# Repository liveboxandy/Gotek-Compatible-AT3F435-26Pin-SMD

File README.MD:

Initial schematic and gerbers for a Gotek(?) compatible with an Artery AT32F435RGT7 chip and a 26 Pin FFC connector using SMD components.
Used SFRKC30.AT4.35 PCB for most of the schematic and layout but used SFRC2D.B PCB for the 26 Pin FFC connections.
Used photographs and a multimeter along with removing U1 and U3 on the SFRKC30.AT4.35 to get to the traces underneath.
Where possible I followed the original PCB routing of the SFRKC30.AT4.35 but Kicad has some different rules for trace widths (between pins 5&6 of U8).
Using SMD components required a few more routing changes but electrically it should still be good.

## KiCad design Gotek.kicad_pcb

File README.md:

# Gotek-Compatible-AT3F435-26Pin-SMD

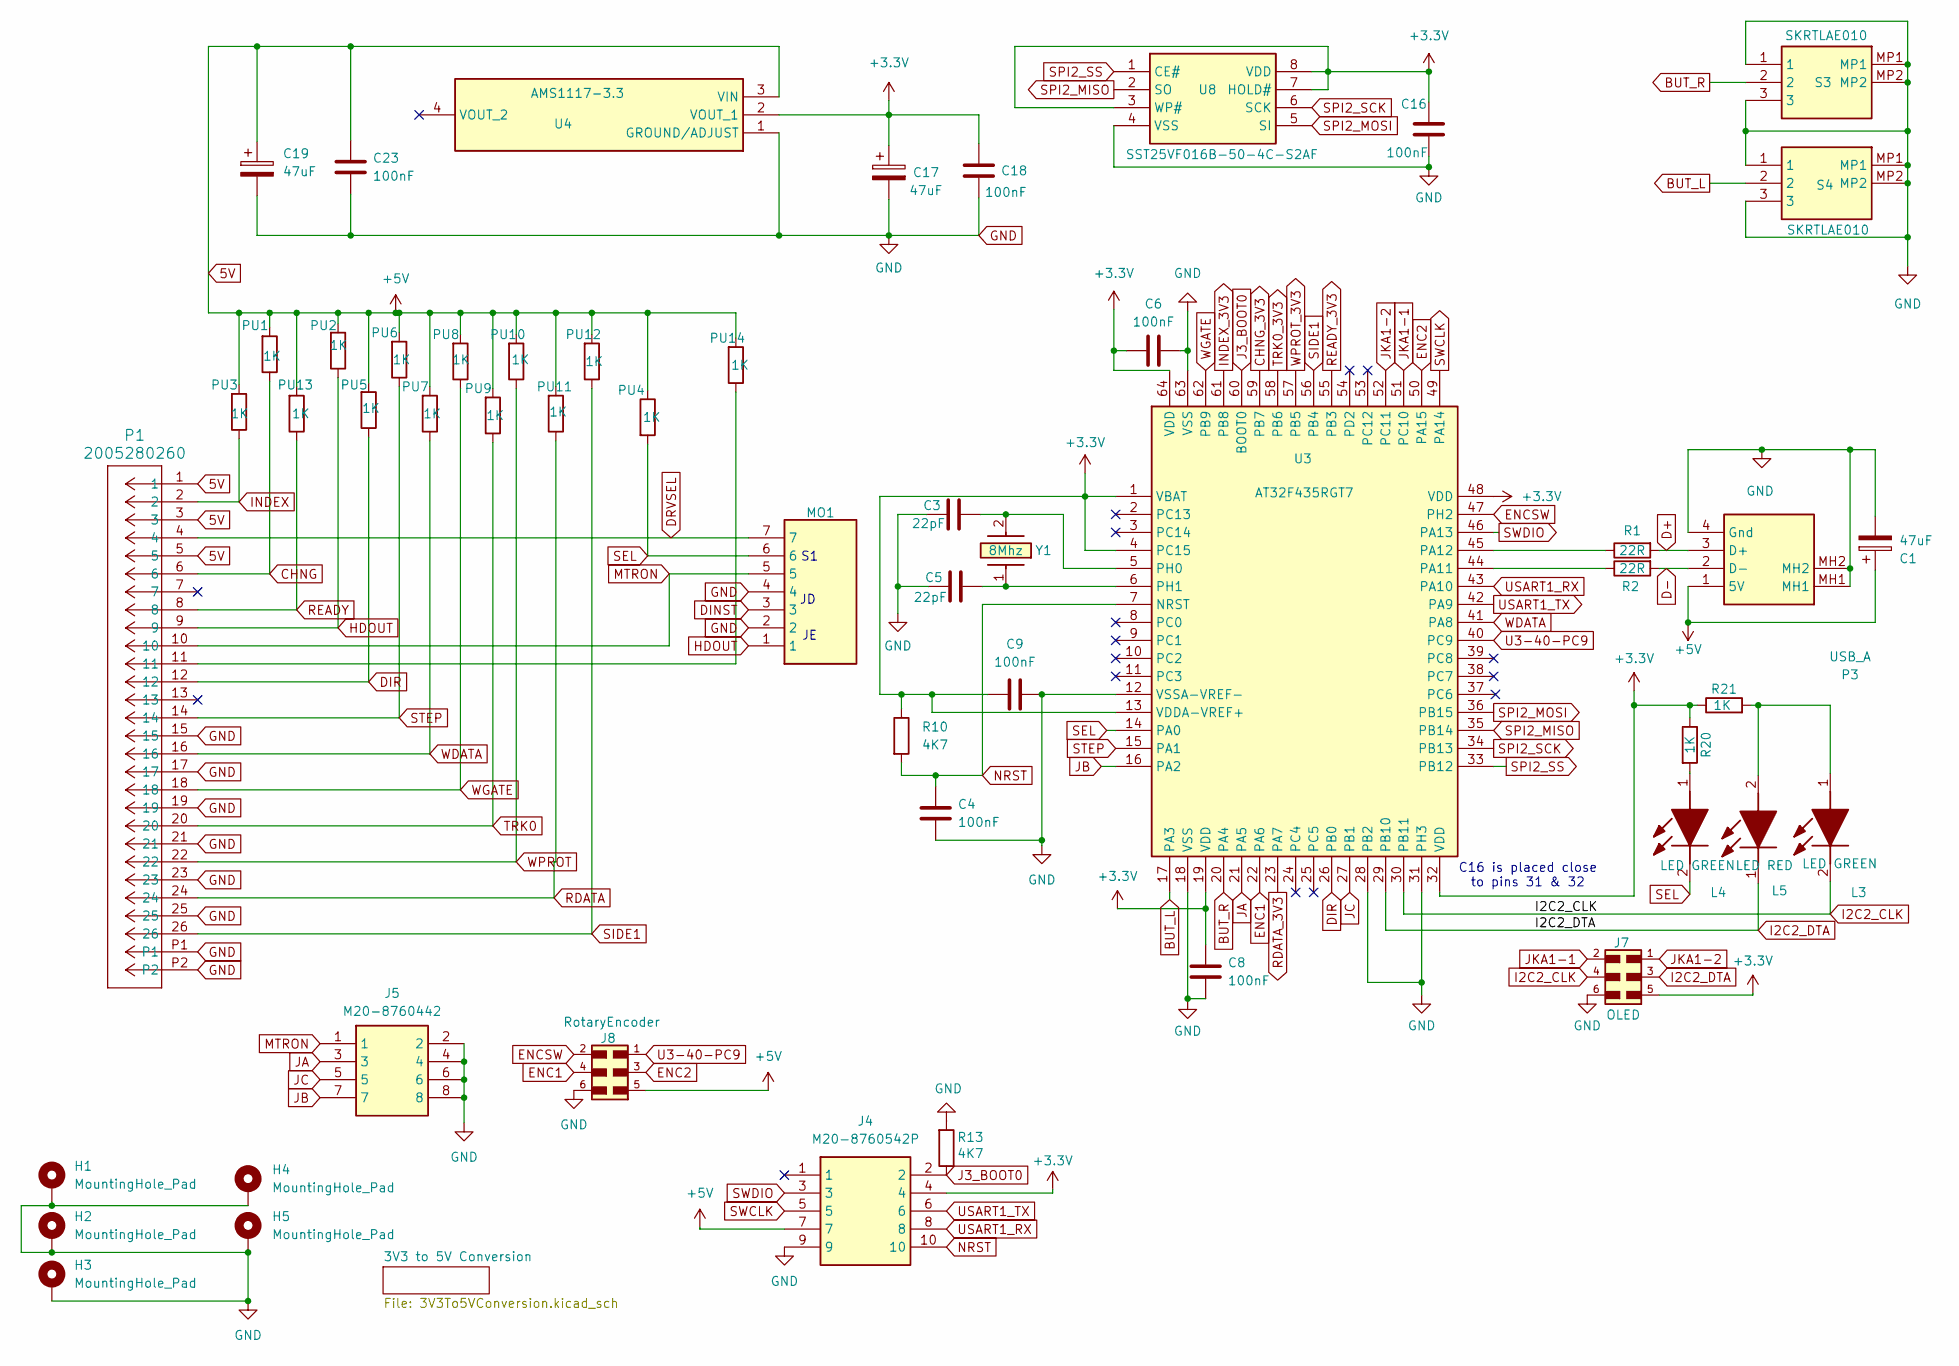
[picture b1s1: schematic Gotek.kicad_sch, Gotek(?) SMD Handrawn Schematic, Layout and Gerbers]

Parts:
C1, C17, C19: 47uF; CP_EIA-3528-21_Kemet-B_Pad1.50x2.35mm_HandSolder
C3, C5: 22pF; C_0805_2012Metric_Pad1.18x1.45mm_HandSolder
C4, C6, C8, C9, C16, C18, C23: 100nF; C_0805_2012Metric_Pad1.18x1.45mm_HandSolder
H1, H2, H3, H4, H5: MountingHole_Pad; MountingHole_M3_Pad
J4: M20-8760542P; HUSSP10W64P254_2X5_1270X500X1043P; Mouser Part Number 855-M20-8760542P
J5: M20-8760442; M208760442; Mouser Part Number 855-M20-8760442
J7: OLED; 610106249121
J8: RotaryEncoder; 610106249121
L3, L4: LED GREEN; APT2012PGW; Mouser Part Number 604-APT2012PGW
L5: LED RED; HSMCC177; Mouser Part Number 630-HSMC-C177
MO1: Conn_01x03_Pin; M208900705; Mouser Part Number 855-M20-8900705
P1: 2005280260; MOLEX_CON_2005280260
P3: USB_A; USB1046GF0190LBA; Mouser Part Number 640-USB1046GF0190LBA
PU1, PU2, PU3, PU4, PU5, PU6, PU7, PU8, PU9, PU10, PU11, PU12, PU13, PU14: 1K; R_0805_2012Metric_Pad1.20x1.40mm_HandSolder
R1, R2: 22R; R_0805_2012Metric_Pad1.20x1.40mm_HandSolder
R10, R13: 4K7; R_0805_2012Metric_Pad1.20x1.40mm_HandSolder
R20, R21: 1K; R_0805_2012Metric_Pad1.20x1.40mm_HandSolder
S3, S4: SKRTLAE010; Mouser Part Number 688-SKRTLA
U3: AT32F435RGT7; QFP50P1200X1200X160-64N; Manufacturer_Part_Number AT32F435RGT7
U4: AMS1117-3.3; SOT229P700X180-4N; Manufacturer_Part_Number ams1117-3.3v
U8: SST25VF016B-50-4C-S2AF; SOIC127P790X216-8N; Mouser Part Number 579-25VF016B504CS2AF
Y1: 8Mhz; LFXTAL050985Bulk; Mouser Part Number 449-LFXTAL050985BULK

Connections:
5V: C1.1, C19.1, C23.1, J4.7, J8.5, P1.1, P1.3, P1.5, P3.1 (5V), PU1.2, PU2.2, PU3.2, PU4.1, PU5.2, PU6.2, PU7.2, PU8.2, PU9.2, PU10.2, PU11.2, PU12.2, PU13.2, PU14.2, U4.3 (VIN); also elsewhere on the board
+3.3V: C6.1, C8.1, C9.2, C16.2, C17.1, C18.2, J4.4, J7.5, R10.1, R20.1, R21.1, U3.1 (VBAT), U3.4 (PC15), U3.13 (VDDA-VREF+), U3.19 (VDD), U3.32 (VDD), U3.48 (VDD), U3.64 (VDD), U4.2 (VOUT_1), U8.3 (WP#), U8.7 (HOLD#), U8.8 (VDD)
BUT_L: S4.2, U3.17 (PA3)
BUT_R: S3.2, U3.20 (PA4)
CHNG: P1.6, PU1.1; also elsewhere on the board
CHNG_3V3: U3.59 (PB7); also elsewhere on the board
D+: P3.3 (D+), R1.2
D-: P3.2 (D-), R2.2
DINST: MO1.3
DIR: P1.12, PU5.1, U3.26 (PB0)
DRVSEL: MO1.7, P1.4
ENC1: J8.4, U3.22 (PA6)
ENC2: J8.3, U3.50 (PA15)
ENCSW: J8.2, U3.47 (PH2)
GND: C1.2, C3.1, C4.2, C5.2, C6.2, C8.2, C9.1, C16.1, C17.2, C18.1, C19.2, C23.2, H1.1, H2.1, H3.1, H4.1, H5.1, J4.9, J5.2, J5.4, J5.6, J5.8, J7.6, J8.6, MO1.2, MO1.4, P1.15, P1.17, P1.19, P1.21, P1.23, P1.25, P1.P1, P1.P2, P3.4 (Gnd), P3.MH1, P3.MH2, R13.2, S3.1, S3.3, S3.MP1, S3.MP2, S4.1, S4.3, S4.MP1, S4.MP2, U3.12 (VSSA-VREF-), U3.18 (VSS), U3.28 (PB2), U3.31 (PH3), U3.63 (VSS), U4.1 (GROUND/ADJUST), U8.4 (VSS); also elsewhere on the board
HDOUT: MO1.1, P1.9, PU2.1
I2C2_CLK: J7.4, L3.2 (K), U3.30 (PB11)
I2C2_DTA: J7.3, L5.1 (K), U3.29 (PB10)
INDEX: P1.2, PU3.1; also elsewhere on the board
INDEX_3V3: U3.61 (PB8); also elsewhere on the board
J3_BOOT0: J4.2, R13.1, U3.60 (BOOT0)
JA: J5.3, U3.21 (PA5)
JB: J5.7, U3.16 (PA2)
JC: J5.5, U3.27 (PB1)
JKA1-1: J7.2, U3.51 (PC10)
JKA1-2: J7.1, U3.52 (PC11)
MTRON: J5.1, MO1.5, P1.10
NRST: C4.1, J4.10, R10.2, U3.7 (NRST)
unnamed: L3.1 (A), L5.2 (A), R21.2
unnamed: L4.1 (A), R20.2
unnamed: P1.11, PU14.1
unnamed: R2.1, U3.44 (PA11)
unnamed: R1.1, U3.45 (PA12)
unnamed: C3.2, U3.5 (PH0), Y1.2
unnamed: C5.1, U3.6 (PH1), Y1.1
RDATA: P1.24, PU11.1; also elsewhere on the board
RDATA_3V3: U3.23 (PA7); also elsewhere on the board
READY: P1.8, PU13.1; also elsewhere on the board
READY_3V3: U3.55 (PB3); also elsewhere on the board
SEL: L4.2 (K), MO1.6, PU4.2, U3.14 (PA0)
SIDE1: P1.26, PU12.1, U3.56 (PB4)
SPI2_MISO: U3.35 (PB14), U8.2 (SO)
SPI2_MOSI: U3.36 (PB15), U8.5 (SI)
SPI2_SCK: U3.34 (PB13), U8.6 (SCK)
SPI2_SS: U3.33 (PB12), U8.1 (CE#)
STEP: P1.14, PU6.1, U3.15 (PA1)
SWCLK: J4.5, U3.49 (PA14)
SWDIO: J4.3, U3.46 (PA13)
TRK0: P1.20, PU9.1; also elsewhere on the board
TRK0_3V3: U3.58 (PB6); also elsewhere on the board
U3-40-PC9: J8.1, U3.40 (PC9)
USART1_RX: J4.8, U3.43 (PA10)
USART1_TX: J4.6, U3.42 (PA9)
WDATA: P1.16, PU7.1, U3.41 (PA8)
WGATE: P1.18, PU8.1, U3.62 (PB9)
WPROT: P1.22, PU10.1; also elsewhere on the board
WPROT_3V3: U3.57 (PB5); also elsewhere on the board

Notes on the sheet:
C16 is placed close to pins 31 & 32

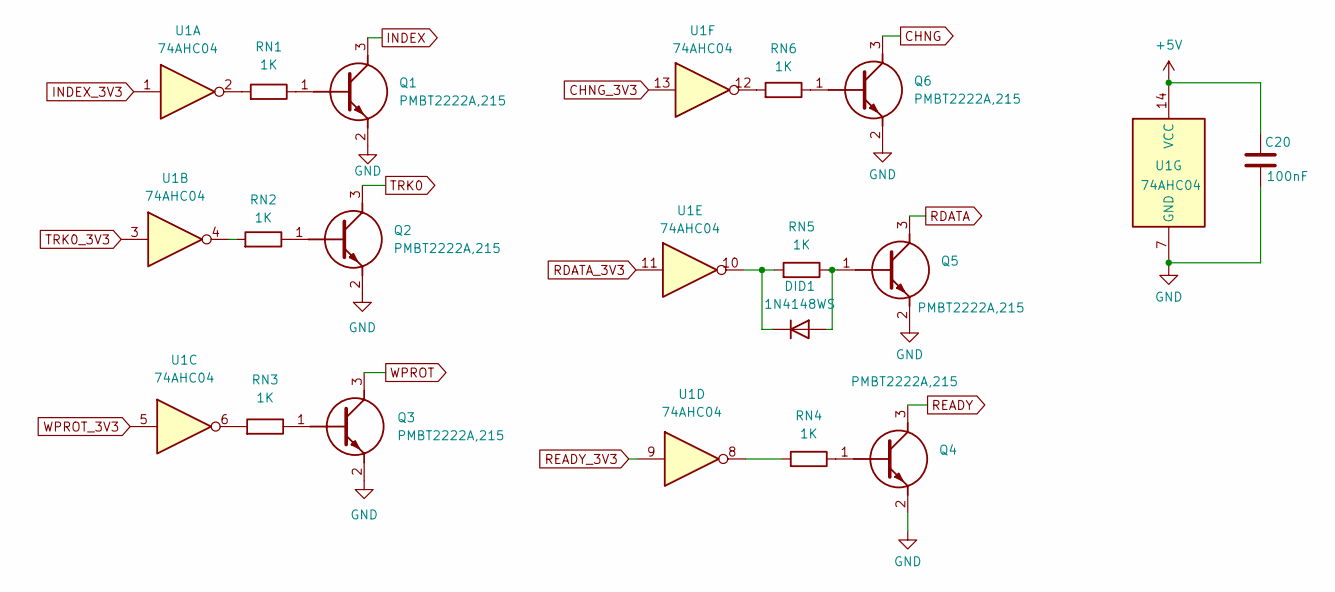
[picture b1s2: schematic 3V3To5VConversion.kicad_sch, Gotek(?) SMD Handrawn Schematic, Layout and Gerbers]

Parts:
C20: 100nF; C_0805_2012Metric_Pad1.18x1.45mm_HandSolder
DID1: 1N4148WS; SODFL2512X90N
Q1, Q2, Q3, Q4, Q5, Q6: PMBT2222A,215; SOT95P280X130-3N; Mouser Part Number 771-PMBT2222A-T/R
RN1, RN2, RN3, RN4, RN5, RN6: 1K; R_0805_2012Metric_Pad1.20x1.40mm_HandSolder
U1: 74AHC04; SO-14_3.9x8.65mm_P1.27mm

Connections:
5V: C20.2, U1.14 (VCC); also elsewhere on the board
CHNG: Q6.3 (C); also elsewhere on the board
CHNG_3V3: U1.13; also elsewhere on the board
GND: C20.1, Q1.2 (E), Q2.2 (E), Q3.2 (E), Q4.2 (E), Q5.2 (E), Q6.2 (E), U1.7 (GND); also elsewhere on the board
INDEX: Q1.3 (C); also elsewhere on the board
INDEX_3V3: U1.1; also elsewhere on the board
unnamed: DID1.2 (A), Q5.1 (B), RN5.1
unnamed: DID1.1 (K), RN5.2, U1.10
unnamed: Q1.1 (B), RN1.1
unnamed: Q2.1 (B), RN2.1
unnamed: Q3.1 (B), RN3.1
unnamed: Q4.1 (B), RN4.1
unnamed: Q6.1 (B), RN6.1
unnamed: RN1.2, U1.2
unnamed: RN2.2, U1.4
unnamed: RN3.2, U1.6
unnamed: RN4.2, U1.8
unnamed: RN6.2, U1.12
RDATA: Q5.3 (C); also elsewhere on the board
RDATA_3V3: U1.11; also elsewhere on the board
READY: Q4.3 (C); also elsewhere on the board
READY_3V3: U1.9; also elsewhere on the board
TRK0: Q2.3 (C); also elsewhere on the board
TRK0_3V3: U1.3; also elsewhere on the board
WPROT: Q3.3 (C); also elsewhere on the board
WPROT_3V3: U1.5; also elsewhere on the board

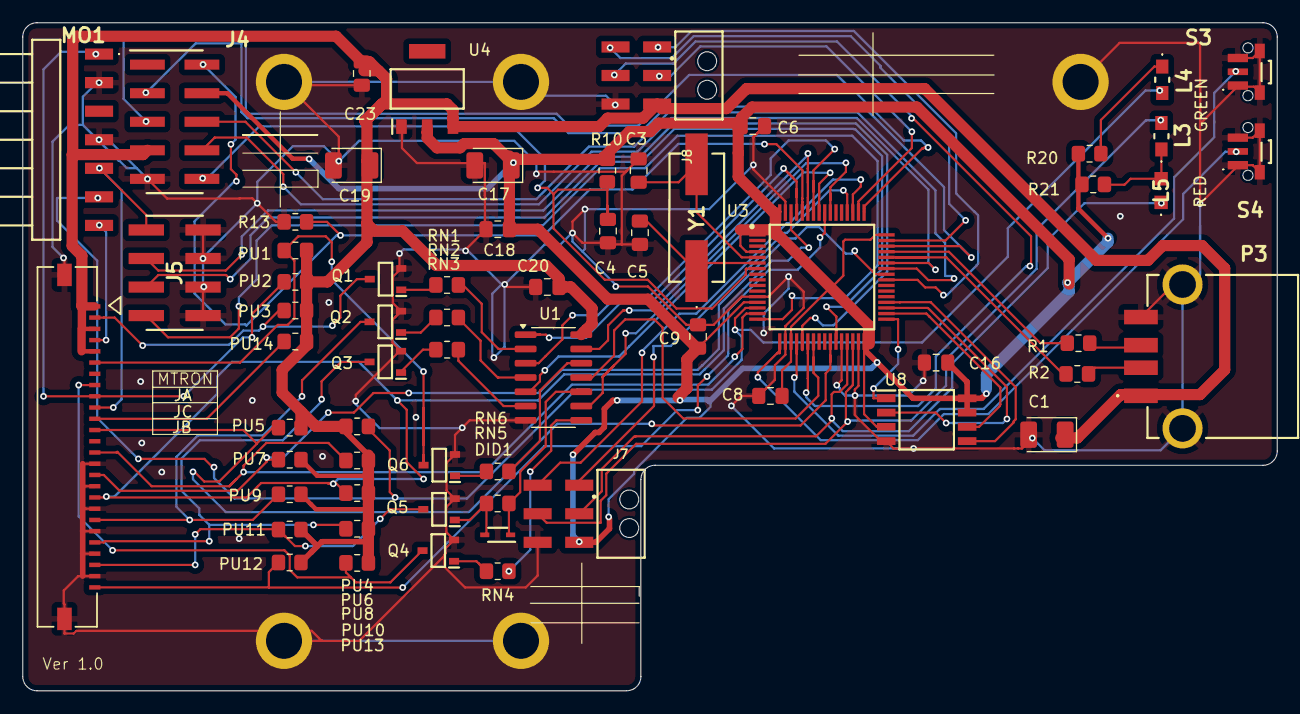
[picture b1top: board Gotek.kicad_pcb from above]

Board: 2 copper layers, 111.6 x 59.4 mm, 68 parts (0 on the bottom side), 68 nets.

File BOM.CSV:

"Reference","Value","Datasheet","Footprint","Qty","DNP"
"C1,C17,C19","47uF","~","Capacitor_Tantalum_SMD:CP_EIA-3528-21_Kemet-B_Pad1.50x2.35mm_HandSolder","3",""
"C3,C5","22pF","~","Capacitor_SMD:C_0805_2012Metric_Pad1.18x1.45mm_HandSolder","2",""
"C4,C6,C8,C9,C16,C18,C20,C23","100nF","~","Capacitor_SMD:C_0805_2012Metric_Pad1.18x1.45mm_HandSolder","8",""
"DID1","1N4148WS","https://www.vishay.com/docs/85751/1n4148ws.pdf","Gotek:SODFL2512X90N","1",""
"J4","M20-8760542P","https://cdn.harwin.com/pdfs/M20-876P.pdf","Gotek:HUSSP10W64P254_2X5_1270X500X1043P","1",""
"J5","M20-8760442","https://cdn.harwin.com/pdfs/M20-876.pdf","Gotek:M208760442","1",""
"J7","OLED","~","Gotek:610106249121","1",""
"J8","RotaryEncoder","~","Gotek:610106249121","1",""
"L3,L4","LED GREEN","~","Gotek:APT2012PGW","2",""
"L5","LED RED","https://docs.broadcom.com/doc/AV02-0975EN","Gotek:HSMCC177","1",""
"MO1","Conn_01x03_Pin","https://cdn.harwin.com/pdfs/M20-890.pdf","Gotek:M208900705","1",""
"P1","2005280260","2005280260","Gotek:MOLEX_CON_2005280260","1",""
"P3","USB_A","https://gct.co/files/drawings/usb1046.pdf?v=ccb5d20d-0631-42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","Gotek:USB1046GF0190LBA","1",""
"PU1,PU2,PU3,PU4,PU5,PU6,PU7,PU8,PU9,PU10,PU11,PU12,PU13,PU14,R20,R21,RN1,RN2,RN3,RN4,RN5,RN6","1K","~","Resistor_SMD:R_0805_2012Metric_Pad1.20x1.40mm_HandSolder","22",""
"Q1,Q2,Q3,Q4,Q5,Q6","PMBT2222A,215","https://assets.nexperia.com/documents/data-sheet/PMBT2222A.pdf","Gotek:SOT95P280X130-3N","6",""
"R1,R2","22R","~","Resistor_SMD:R_0805_2012Metric_Pad1.20x1.40mm_HandSolder","2",""
"R10,R13","4K7","~","Resistor_SMD:R_0805_2012Metric_Pad1.20x1.40mm_HandSolder","2",""
"S3,S4","SKRTLAE010","https://tech.alpsalpine.com/e/products/detail/SKRTLAE010/","Gotek:SKRTLAE010","2",""
"U1","74AHC04","https://assets.nexperia.com/documents/data-sheet/74AHC_AHCT04.pdf","Package_SO:SO-14_3.9x8.65mm_P1.27mm","1",""
"U3","AT32F435RGT7","","Gotek:QFP50P1200X1200X160-64N","1",""
"U4","AMS1117-3.3","http://www.advanced-monolithic.com/pdf/ds1117.pdf","Gotek:SOT229P700X180-4N","1",""
"U8","SST25VF016B-50-4C-S2AF","https://ww1.microchip.com/downloads/en/DeviceDoc/20005044C.pdf","Gotek:SOIC127P790X216-8N","1",""
"Y1","8Mhz","https://componentsearchengine.com/Datasheets/1/LFXTAL050985Bulk.pdf","Gotek:LFXTAL050985Bulk","1",""

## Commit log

2025-03-06 Add files via upload
    Initial upload of files without component pdfs and mod/sym/stp files
2025-03-06 Add files via upload
    Include some component pdfs and zips of mod/sym/stp files
2025-03-06 Add files via upload
    Add Mod folder for Kicad. Includes kicad_mod, Kicad_sym and 3d stp/step files.
2025-04-11 Add files via upload
    Schematic and gerbers for a Gotek(?) compatible with an Artery AT32F435RGT7 chip and a 26 Pin FFC connector.
    Used SFRKC30.AT4.35 PCB for most of the schematic and layout but used SFRC2D.B PCB for the 26 Pin FFC connections.
    Used photographs and a multimeter along with removing U1 and U3 on the SFRKC30.AT4.35 to get to the traces underneath.
    Where possible I followed the original PCB routing of the SFRKC30.AT4.35 but Kicad has some different rules for trace widths (between pins 5&6 of U8 which isn't fitted).
    Removed L3 Green LED and changed R21 to 12K to reduce it's brightness. Also increased the pad sizes for the diode D1D to make it easier to hand solder. Minor chan
